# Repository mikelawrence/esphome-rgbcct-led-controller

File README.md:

# ESPHome RGBCCT LED Controller

<p align="center">
  
</p>

This project evolved from the need to support LED strips for growing African Violets. It is surprising how much light plants need and how little light LED strip actually put out. My original approach was three strips composed of Cool White (CW) and Warm White LEDs (WW). But it wasn't until I purchased a Photosynthetically Active Radiation (PAR) meter to measure the Photosynthetic Photon Flux Density (PPFD, units µmol/m²/s) just how un-bright my setup was. These units are interesting. The first part, µmol, is a number, specifically one-millionth of a mole, or 6.022 x 10²³ / 1,000,000 or 6.022 x 10¹⁷. The second part is an area, 1 meter squared. And finally time in seconds. When put together it is basically the number of photons striking a one meter squared area per second. Most measurements of light intensity, like lux, lumens, or luminance, are based on human perception are not really good for plants so PAR/PPFD was developed in the 1970s by Dr. Keith McCree. When I measured the light output of my setup with my shiny new PAR meter I got 20PPFD with my original setup of three strips of CW and WW LEDs between 60 and 200PPFD. There is different and sometimes conflicting information on the Internet but the range I found for African Violets is somewhere between 60 and 200PPFD. So my setup was three times less than minimum of 60PPFD.

Clearly I need more light. I started looking on Internet for "brighter" LED strips. I found [these](https://www.superlightingled.com/dc24v-112ledsm-highest-density-5in1-rgbww-led-strip-smd5050-164ft-p-5599.html) from SUPERLIGHTINGLED they have 5 different LEDS, Red, Green, Blue, Warm White and Cool Light. This is five PWM channels which reduces the available controllers to only a few but I did find a Zigbee 5-channel controller. But the control of the LEDs are difficult. What I really needed was to turn on all LEDS simultaneously and this controller could not so this with Home Assistant. It also adjust the light intensity with gamma which again is based on human perception. I found another controller from GLEDOPTO with WLED installed which gave me chance to control everything in the way I wanted and that is when I realized turning all the LEDS on at the same time caused them to warm up to more than 50°C. Not necessarily a problem but one that would probably shorten the life of the strips. I ended up with five of these LED strips per shelf running at a reduced intensity and still have 80PPFD.

Now that the light levels are in better range I decided to design my own LED controller because I wanted to add 4-Pin computer fan control and temperature measurement of both ambient and some of the LED strips to make sure I wasn't getting them too hot.

This LED controller supports the following:

* ESP32-S3
* ESPHome software development
* USB-C Interface for initial/ongoing programming, OTA will still be the primary mean of programming
* Power, Voltage and Current measurement with an INA232
* 5-Channel PWM LED control
* Supporting 5-24V Vin, this same voltage is applied to the LED and fan
* Two configurations: One supporting 5A and with the addition of two transistors 10A total current
* Each channel comfortably supports 2A simultaneous and up to 3-4A singly
* Vin is well protected
  * No damage input range is ±33V, TVS will adsorb higher transients
  * Over current shutdown
  * Over temperature shutdown
  * Short circuit shutdown
  * Reverse Polarity shutdown
  * Over Voltage Lockout
  * Under Voltage Lockout
* PCB temperature measurement near the Vin protection circuit. This is broken.
* Each channel is a protected MOSFET, if will shutdown when over temperature and will take a short to ground without damage
* With the addition of an expansion board
  * LED strip temperature measurement with 10K thermistors.
  * Ambient temperature measurement with a commonly available SHTXX I²C sensor

## Main PCB

<p align="center">
  
</p>

View the [README](pcb/README.md) for more information about this PCB.

## Temperature Expansion PCBs

<p align="center">

</p>

View the [Rev A README](pcb-expansion-rev-a/README.md) or [Rev B README](pcb-expansion-rev-b/README.md) for more information.

## Configuration

[RGBCCT LED Controller GH Pages](https://mikelawrence.github.io/esphome-rgbcct-led-controller/) provides installation and Home Assistant configuration support.

## Web Server

Th Web Server is enabled in the current configuration. The default username is `light` and password is `password`. Auth is enabled mainly because manual firmware updates are enabled in the Web Server.

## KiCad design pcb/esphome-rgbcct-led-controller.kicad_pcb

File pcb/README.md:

# ESPHome RGBCCT LED Controller PCB

The PCB is designed in [KiCad](https://www.kicad.org/). Fabrication and is tuned toward [JCLPCB](https://jlcpcb.com/). I using my [Whizoo Controleo3](https://whizoo.com/) oven to handle all but the Thru-Hole stuff which is hand soldered.

* **Rev A**: Has been fabricated, assembled, tested and is use in four places. There is one issue TMP1075 (U1) is connected to VINP and will burn when powered by 24V and must be left off the PCB.

## Testing Notes

Only the 5A configuration has been tested. Short circuit on LED outputs will not damage the board but the red LED will not light up. This type of short circuits will recover automatically recover when removed. Short circuits on the fan connector will shut off power to everything and cause the red LED to light up. Short circuits of this type are latching and require power-cycling to release. Over-voltage and Under-Voltage Lock Out work fine. The 4-Pin fan connector supports fans but the PWM signal is 1.5kHz well below the recommended 25kHz. There seems to be an issue with the ledc component the prevents different pwm frequencies when using 6 ledc channels. 1.5kHz work well with Noctua fans.

## Schematic

<p align="center">
     <br />
    Schematic
</p>

### Do Not Populate (DNP) Notes

TMP1075 (U1) cannot be populated due to a PCB error. It will burn with 24V Vin.

## Bill of Materials

<p align="center">
     <br />
    Interactive BOM
</p>

## PCB Info

* 6 layers with many vias to support high currents. Vias should be filled to improve thermals.
* Two configurations, 5A Continuous, 10A Short Circuit and 10A Continuous and 20A Short Circuit.
* Dimensions are 100mm X 45mm.
* Requires oven reflow or hot air to assemble most components.

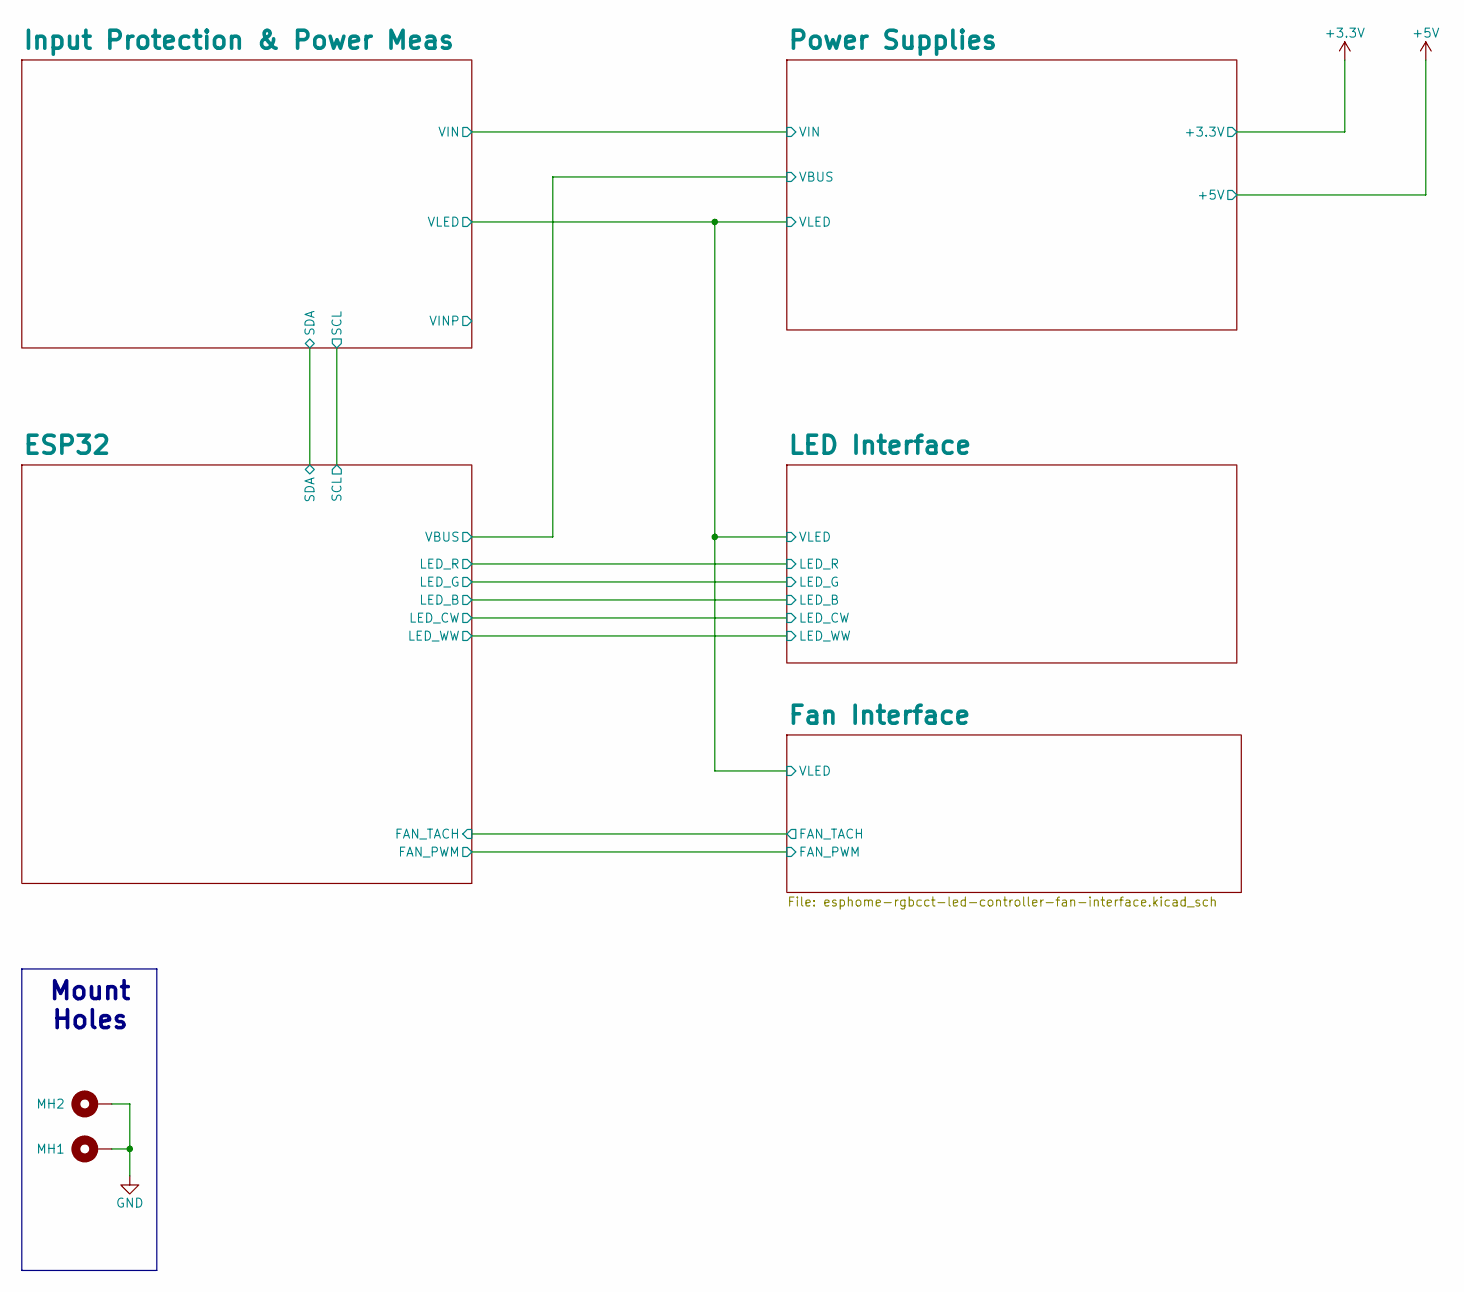
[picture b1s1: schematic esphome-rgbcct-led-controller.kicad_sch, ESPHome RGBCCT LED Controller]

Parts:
MH1, MH2: 97730606332R; Part Number 97730606332R

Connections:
GND: MH1.1 (1_1), MH2.1 (1_1); also elsewhere on the board

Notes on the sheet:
Mount Holes

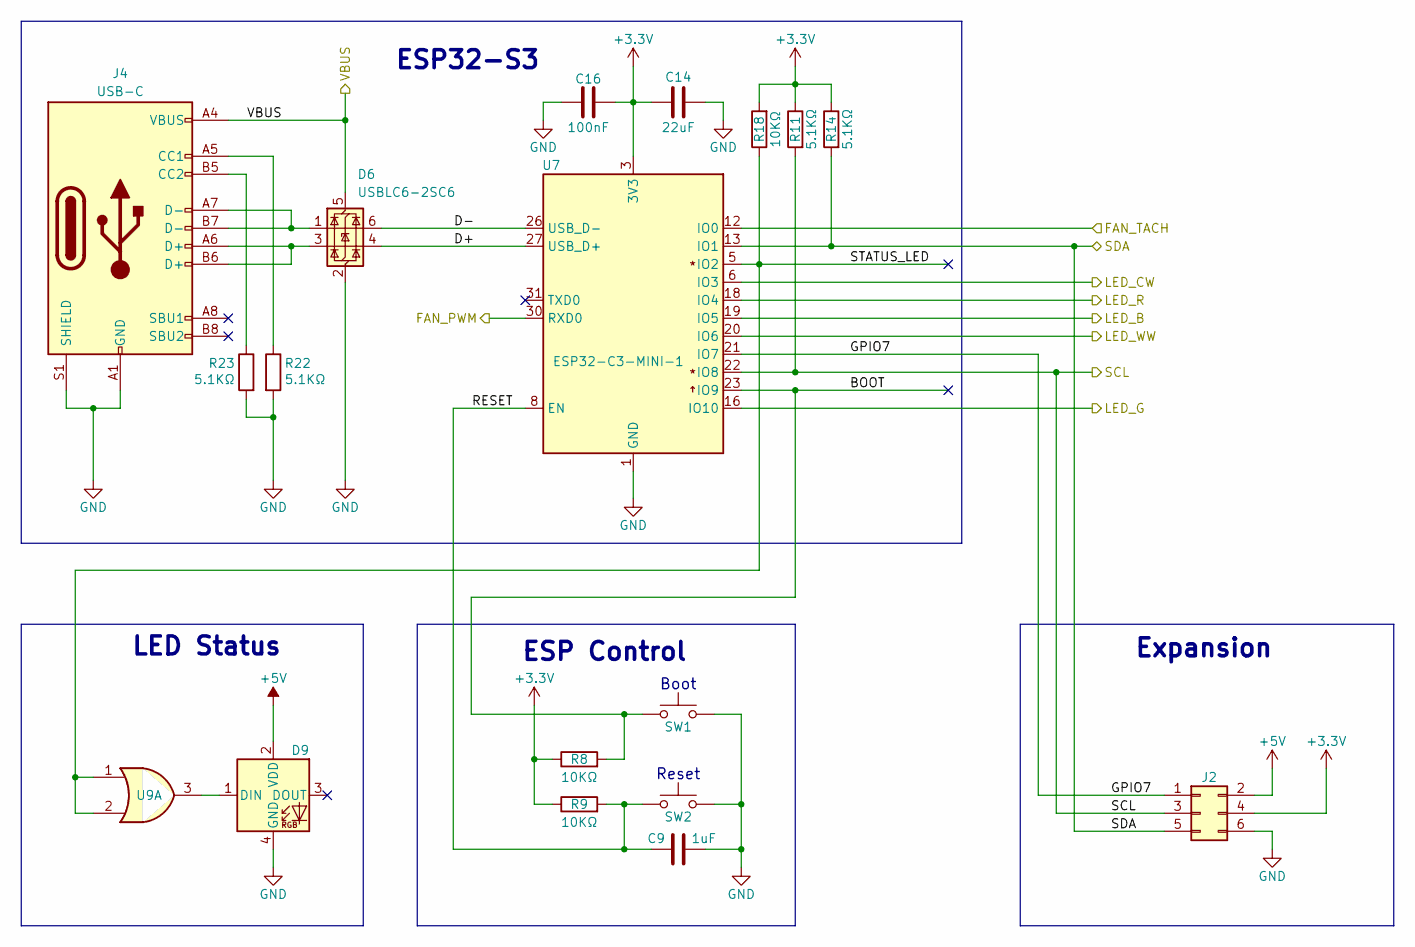
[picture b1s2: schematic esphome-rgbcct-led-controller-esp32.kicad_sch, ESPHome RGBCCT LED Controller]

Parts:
C9: 1uF; C_0402_1005Metric; Part Number GRM155R61H105KE05D
C14: 22uF; C_0603_1608Metric; Part Number GRM188R60J226MEA0D
C16: 100nF; C_0402_1005Metric; Part Number CL05B104KB54PNC
D6: USBLC6-2SC6; SOT-23-6; Part Number USBLC6-2SC6
D9: SK6812-4020; Part Number 4691
J2: SAMTEC_SFMC-103-01-L-D; Part Number SFMC-103-01-L-D
J4: USB-C; HRO_TYPE-C-31-M-12; Part Number 1332645
R8, R9, R18: 10KΩ; R_0402_1005Metric; Part Number CRCW040210K0FKED
R11, R14, R22, R23: 5.1KΩ; R_0402_1005Metric; Part Number CRCW04025K10FKED
SW1, SW2: SW_SPST_B3U-1000P-B; Part Number B3U-1000P
U7: ESP32-C3-MINI-1; ESP32-C3-MINI-1-N4X; Part Number ESP32-C3-MINI-1-N4X
U9: 74AHCT32; DHWQFN-14-1EP_2.5x3mm_P0.5mm_EP1x1.5mm; Part Number SN74AHCT32BQAR

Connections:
+3.3V: C14.1, C16.2, J2.4, R8.1, R9.1, R11.1, R14.1, R18.2, U7.3 (3V3); also elsewhere on the board
+5V: D9.2 (VDD), J2.2; also elsewhere on the board
/ESP32/BOOT: R8.2, SW1.2, U7.23 (IO9)
/ESP32/D+: D6.4 (I/O2), U7.27 (USB_D+)
/ESP32/D-: D6.6 (I/O1), U7.26 (USB_D-)
/ESP32/FAN_PWM: U7.30 (RXD0); also elsewhere on the board
/ESP32/FAN_TACH: U7.12 (IO0); also elsewhere on the board
/ESP32/GPIO7: J2.1, U7.21 (IO7)
/ESP32/LED_B: U7.19 (IO5); also elsewhere on the board
/ESP32/LED_CW: U7.6 (IO3); also elsewhere on the board
/ESP32/LED_G: U7.16 (IO10); also elsewhere on the board
/ESP32/LED_R: U7.18 (IO4); also elsewhere on the board
/ESP32/LED_WW: U7.20 (IO6); also elsewhere on the board
/ESP32/RESET: C9.1, R9.2, SW2.2, U7.8 (EN)
/ESP32/SCL: J2.3, R11.2, U7.22 (IO8); also elsewhere on the board
/ESP32/SDA: J2.5, R14.2, U7.13 (IO1); also elsewhere on the board
/ESP32/STATUS_LED: R18.1, U7.5 (IO2), U9.1, U9.2
/ESP32/VBUS: D6.5 (VBUS), J4.A4 (VBUS), J4.B4 (VBUS); also elsewhere on the board
GND: C9.2, C14.2, C16.1, D6.2 (GND), D9.4 (GND), J2.6, J4.A1 (GND), J4.B1 (GND), J4.S1 (SHIELD), R22.2, R23.2, SW1.1, SW2.1, U7.1 (GND), U7.2 (GND), U7.11 (GND), U7.14 (GND), U7.36 (GND), U7.37 (GND), U7.38 (GND), U7.39 (GND), U7.40 (GND), U7.41 (GND), U7.42 (GND), U7.43 (GND), U7.44 (GND), U7.45 (GND), U7.46 (GND), U7.47 (GND), U7.48 (GND), U7.49 (GND), U7.50 (GND), U7.51 (GND), U7.52 (GND), U7.53 (GND); also elsewhere on the board
unnamed: D6.1 (I/O1), J4.A7 (D-), J4.B7 (D-)
unnamed: D6.3 (I/O2), J4.A6 (D+), J4.B6 (D+)
unnamed: D9.1 (DIN), U9.3
unnamed: J4.A5 (CC1), R22.1
unnamed: J4.B5 (CC2), R23.1

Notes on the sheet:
ESP32-S3
Expansion
Reset
ESP Control
Boot
LED Status

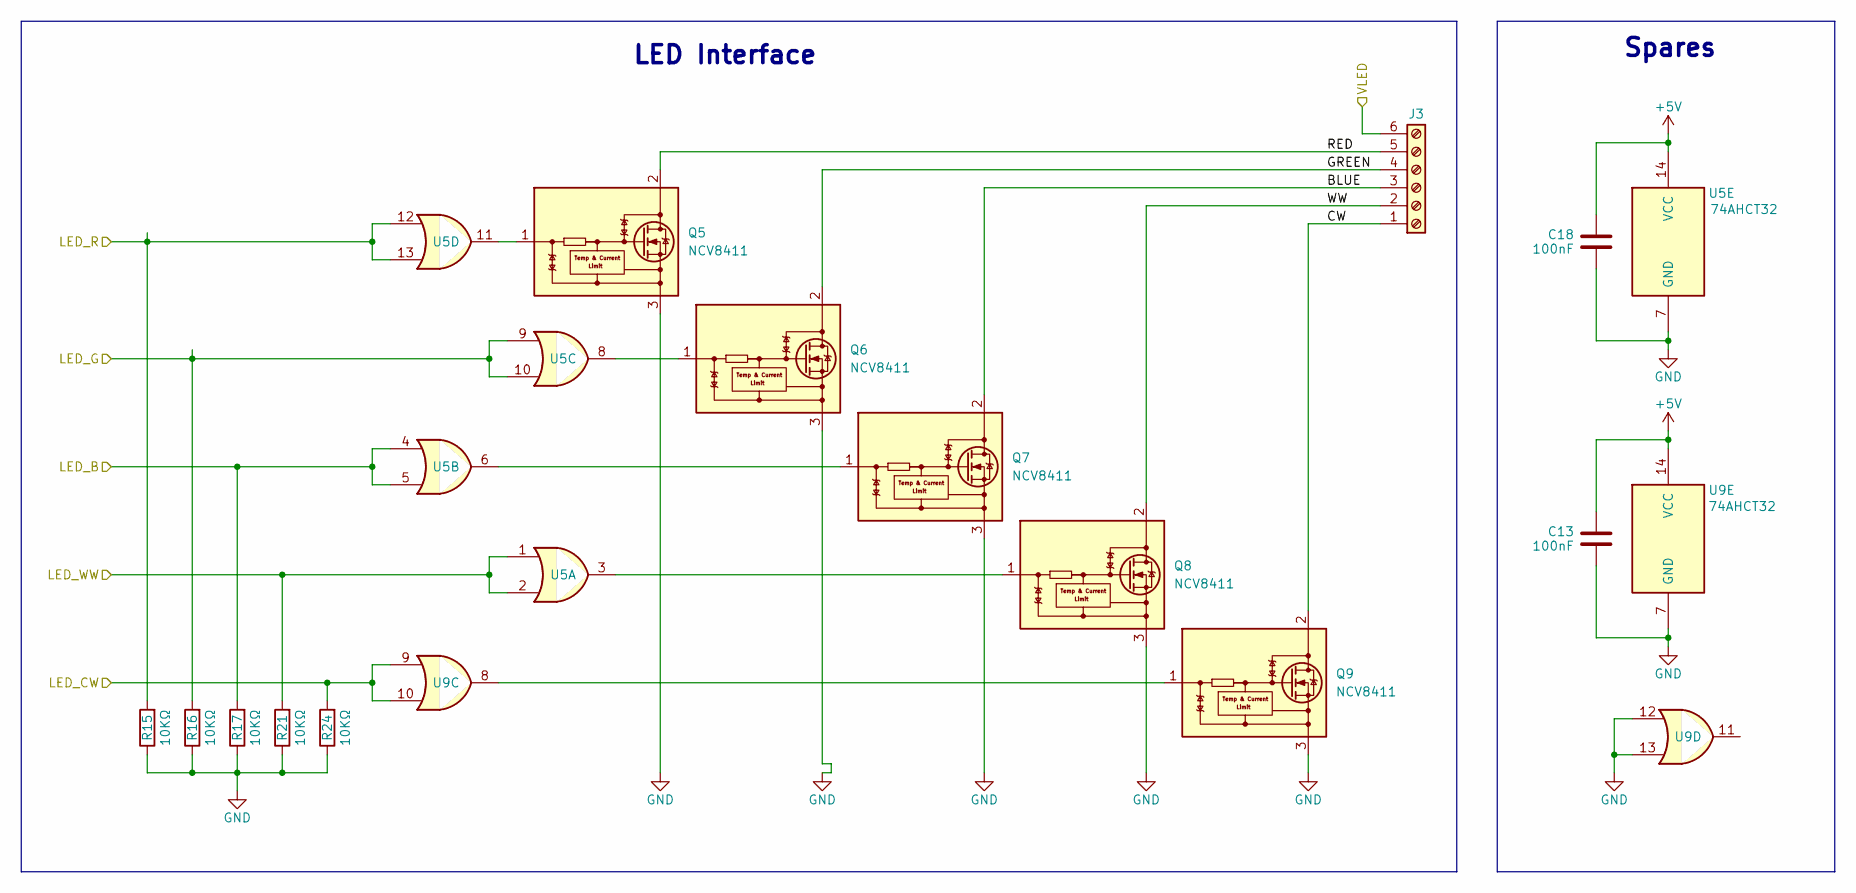
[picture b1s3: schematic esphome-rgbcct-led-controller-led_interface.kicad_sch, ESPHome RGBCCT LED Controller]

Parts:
C13, C18: 100nF; C_0402_1005Metric; Part Number CL05B104KB54PNC
J3: 1017507; Part Number 1017507
Q5, Q6, Q7, Q8, Q9: NCV8411; TO-252-2; Part Number NCV8411DTRKG
R15, R16, R17, R21, R24: 10KΩ; R_0402_1005Metric; Part Number CRCW040210K0FKED
U5, U9: 74AHCT32; DHWQFN-14-1EP_2.5x3mm_P0.5mm_EP1x1.5mm; Part Number SN74AHCT32BQAR

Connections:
+5V: C13.1, C18.1, U5.14 (VCC), U9.14 (VCC); also elsewhere on the board
/ESP32/LED_B: R17.2, U5.4, U5.5; also elsewhere on the board
/ESP32/LED_CW: R24.2, U9.9, U9.10; also elsewhere on the board
/ESP32/LED_G: R16.2, U5.9, U5.10; also elsewhere on the board
/ESP32/LED_R: R15.2, U5.12, U5.13; also elsewhere on the board
/ESP32/LED_WW: R21.2, U5.1, U5.2; also elsewhere on the board
/Fan Interface/VLED: J3.6; also elsewhere on the board
/LED Interface/BLUE: J3.3, Q7.2 (D)
/LED Interface/CW: J3.1, Q9.2 (D)
/LED Interface/GREEN: J3.4, Q6.2 (D)
/LED Interface/RED: J3.5, Q5.2 (D)
/LED Interface/WW: J3.2, Q8.2 (D)
GND: C13.2, C18.2, Q5.3 (S), Q6.3 (S), Q7.3 (S), Q8.3 (S), Q9.3 (S), R15.1, R16.1, R17.1, R21.1, R24.1, U5.7 (GND), U9.7 (GND), U9.12, U9.13; also elsewhere on the board
unnamed: Q5.1 (G), U5.11
unnamed: Q6.1 (G), U5.8
unnamed: Q7.1 (G), U5.6
unnamed: Q8.1 (G), U5.3
unnamed: Q9.1 (G), U9.8

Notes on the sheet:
Spares
LED Interface

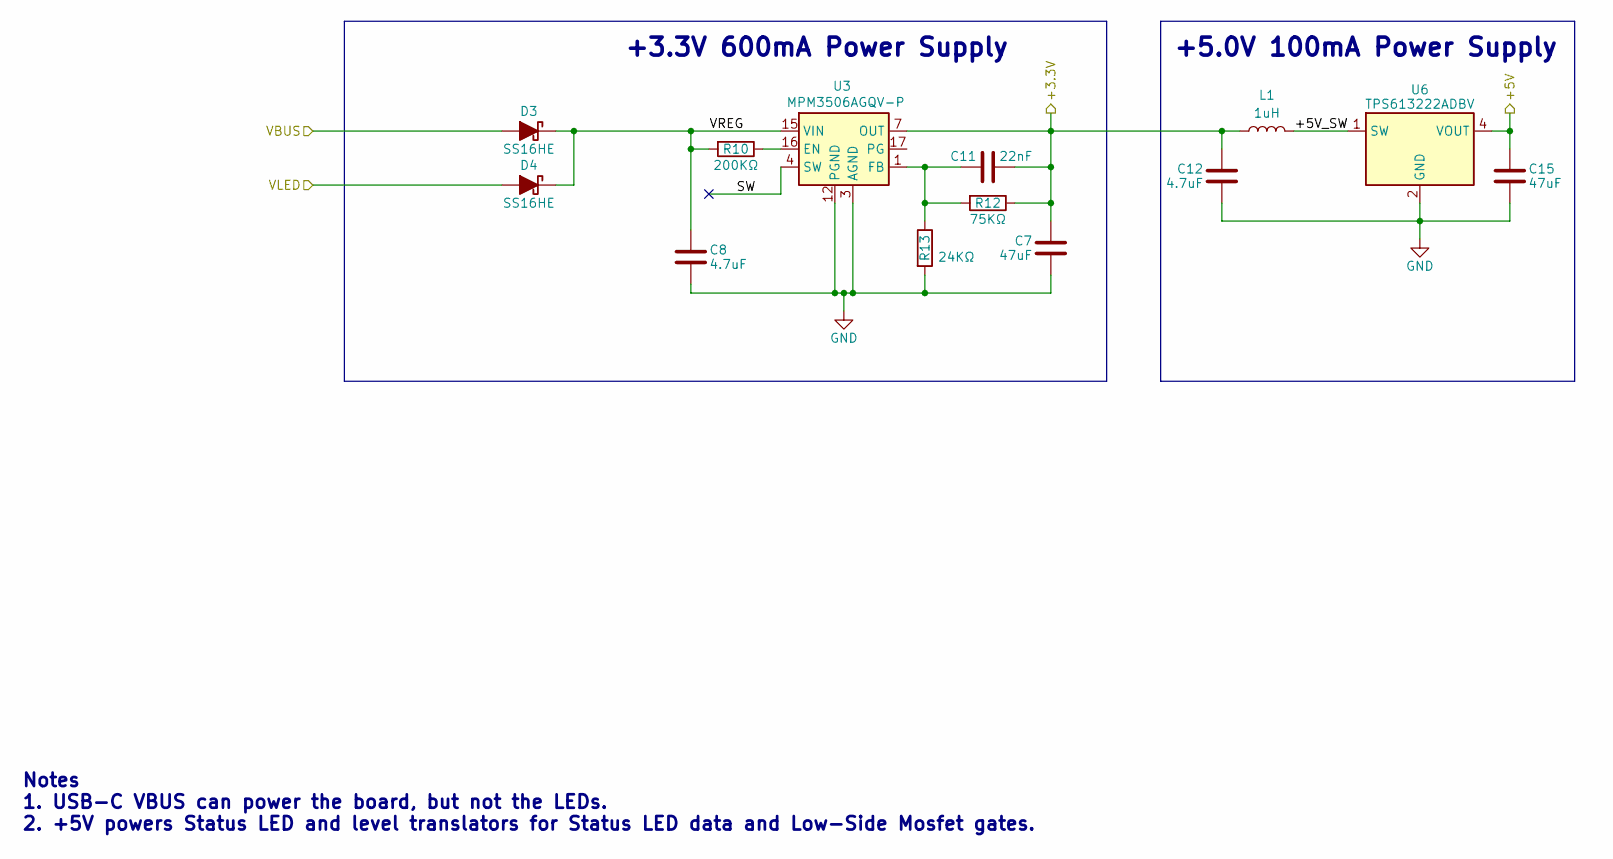
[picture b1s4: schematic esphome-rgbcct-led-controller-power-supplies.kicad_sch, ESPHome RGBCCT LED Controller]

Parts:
C7, C15: 47uF; C_0805_2012Metric; Part Number MSASL21GBB5476MTNA01
C8, C12: 4.7uF; C_0805_2012Metric; Part Number MSASU21GBB5475KTNA01
C11: 22nF; C_0402_1005Metric; Part Number GRM155R71H223KA12J
D3, D4: SS16HE; Part Number SS16HE
L1: 1uH; L_0805_2012Metric; Part Number MLP2012S1R0MT0S1
R10: 200KΩ; R_0402_1005Metric; Part Number CRCW0402200KFKED
R12: 75KΩ; R_0402_1005Metric; Part Number RT0402BRD0775KL
R13: 24KΩ; R_0402_1005Metric; Part Number RT0402BRD0724KL
U3: MPM3506AGQV-P; QFN-19; Part Number MPM3506AGQV-P; Mouser Part Number 946-MPM3506AGQV-P
U6: TPS613222ADBV; SOT-23-5; Part Number TPS613222ADBVR

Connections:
+3.3V: C7.1, C11.2, C12.1, L1.1, R12.1, U3.7 (OUT), U3.8 (OUT_2), U3.9 (OUT_3), U3.19 (OUT_4); also elsewhere on the board
+5V: C15.1, U6.4 (VOUT); also elsewhere on the board
/ESP32/VBUS: D3.2 (A); also elsewhere on the board
/Fan Interface/VLED: D4.2 (A); also elsewhere on the board
/Power Supplies/+5V_SW: L1.2, U6.1 (SW)
/Power Supplies/SW: U3.4 (SW), U3.5 (SW_2), U3.6 (SW_3), U3.18 (SW_4)
/Power Supplies/VREG: C8.1, D3.1 (K), D4.1 (K), R10.2, U3.15 (VIN)
GND: C7.2, C8.2, C12.2, C15.2, R13.2, U3.3 (AGND), U3.12 (PGND), U3.13 (PGND_2), U6.2 (GND); also elsewhere on the board
unnamed: R10.1, U3.16 (EN)
unnamed: C11.1, R12.2, R13.1, U3.1 (FB)

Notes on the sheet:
+5.0V 100mA Power Supply
+3.3V 600mA Power Supply
Notes 1. USB-C VBUS can power the board, but not the LEDs. 2. +5V powers Status LED and level translators for Status LED data and Low-Side Mosfet gates.

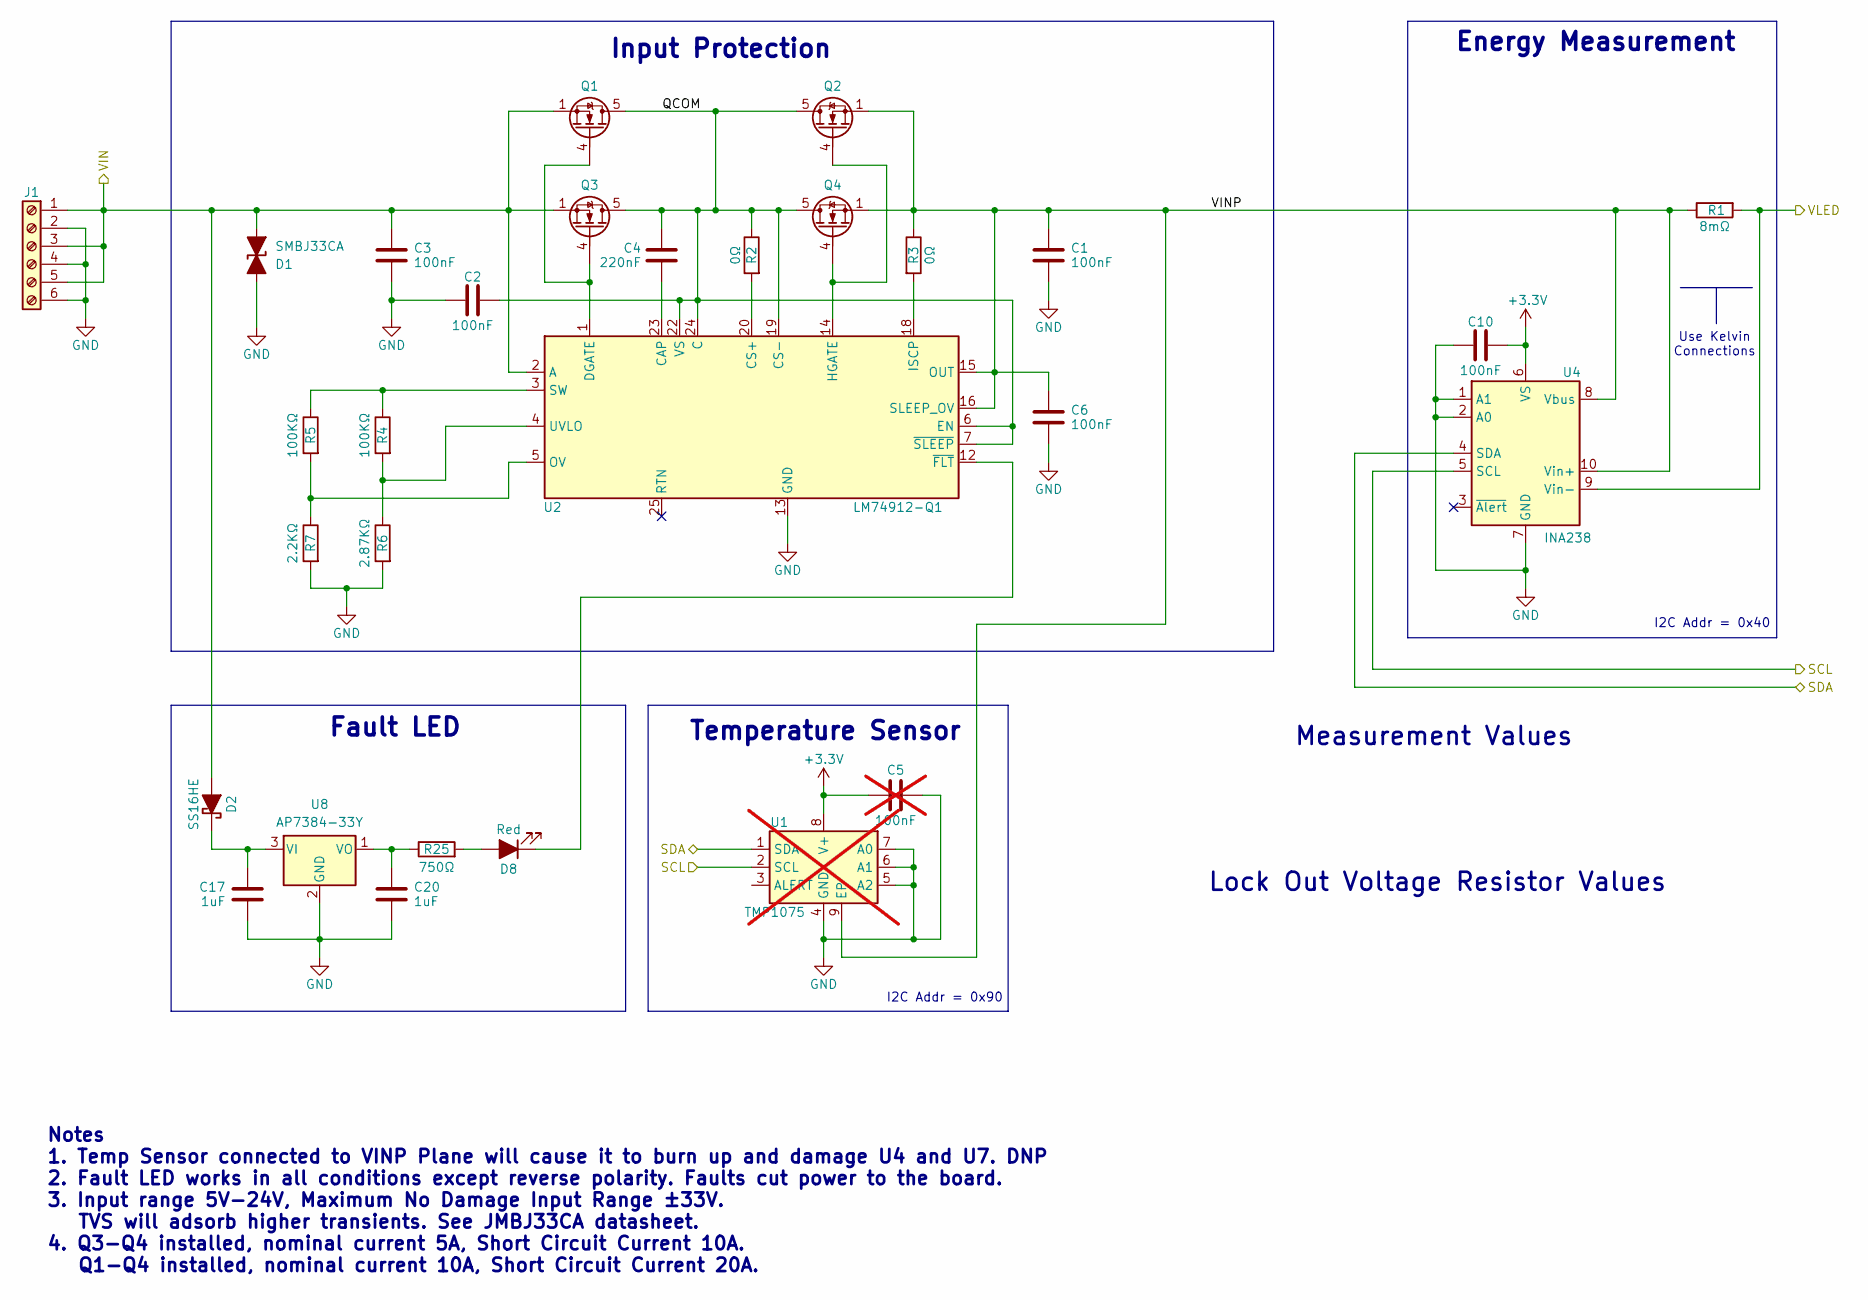
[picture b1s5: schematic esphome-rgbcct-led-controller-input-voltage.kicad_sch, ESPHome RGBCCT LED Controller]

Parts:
C1, C2, C3, C6, C10: 100nF; C_0402_1005Metric; Part Number CL05B104KB54PNC
C4: 220nF; C_0402_1005Metric; Part Number GRM155R61H224ME01W
C5: 100nF; C_0402_1005Metric; Part Number CL05B104KB54PNC; not fitted
C17, C20: 1uF; C_0402_1005Metric; Part Number GRM155R61H105KE05D
D1: SMBJ33CA; D_SMB; Part Number SMBJ33CA
D2: SS16HE; Part Number SS16HE
D8: Red; APDA3020LSECKJ3PF; Part Number APDA3020LSECK/J3-PF
J1: 1017505; 1017507; Part Number 1017505
Q1, Q2, Q3, Q4: TQM050NB06CR; TRANS_TQM050NB06CR_RLG; Part Number TQM050NB06CR RLG
R1: 8mΩ; R_2512_6332Metric; Part Number MSMA2512R0080FGM
R2, R3: 0Ω; R_0402_1005Metric; Part Number RC0402FR-070RL
R4, R5: 100KΩ; R_0402_1005Metric; Part Number RT0402BRD07100KL
R6: 2.87KΩ; R_0402_1005Metric; Part Number RT0402BRD072K87L
R7: 2.2KΩ; R_0402_1005Metric; Part Number RT0402BRD072K2L
R25: 750Ω; R_0402_1005Metric; Part Number CRCW0402750RFKED
U1: TMP1075; WSON-8-1EP_2x2mm_P0.5mm_EP0.9x1.6mm_ThermalVias; Part Number TMP1075DSGR; not fitted
U2: LM74912-Q1; Texas_RGE0024C_VQFN-24-1EP_4x4mm_P0.5mm_EP2.1x2.1mm; Part Number LM74912QRGERQ1
U4: INA238; VSSOP-10_3x3mm_P0.5mm; Part Number INA238AIDGSR
U8: AP7384-33Y; SOT-89-3; Part Number AP7384-33Y-13

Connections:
+3.3V: C5.2, C10.2, U1.8 (V+), U4.6 (VS); also elsewhere on the board
/ESP32/SCL: U1.2 (SCL), U4.5 (SCL); also elsewhere on the board
/ESP32/SDA: U1.1 (SDA), U4.4 (SDA); also elsewhere on the board
/Fan Interface/VLED: R1.2, U4.9 (Vin-); also elsewhere on the board
/Input Protection & Power Meas/QCOM: C2.2, C4.2, Q1.5 (D), Q2.5 (D), Q3.5 (D), Q4.5 (D), R2.1, U2.6 (EN), U2.7 (~SLEEP), U2.19 (CS-), U2.22 (VS), U2.24 (C)
/Input Protection & Power Meas/VIN: C3.1, D1.1 (A1), D2.2 (A), J1.1, J1.3, J1.5, Q1.1 (S), Q1.2 (S), Q1.3 (S), Q3.1 (S), Q3.2 (S), Q3.3 (S), U2.2 (A)
/Input Protection & Power Meas/VINP: C1.1, C6.1, Q2.1 (S), Q2.2 (S), Q2.3 (S), Q4.1 (S), Q4.2 (S), Q4.3 (S), R1.1, R3.1, U1.9 (EP), U2.15 (OUT), U2.16 (SLEEP_OV), U4.8 (Vbus), U4.10 (Vin+)
GND: C1.2, C2.1, C3.2, C5.1, C6.2, C10.1, C17.2, C20.2, D1.2 (A2), J1.2, J1.4, J1.6, R6.2, R7.2, U1.4 (GND), U1.5 (A2), U1.6 (A1), U1.7 (A0), U2.13 (GND), U4.1 (A1), U4.2 (A0), U4.7 (GND), U8.2 (GND); also elsewhere on the board
unnamed: C17.1, D2.1 (K), U8.3 (VI)
unnamed: D8.2 (A), R25.2
unnamed: D8.1 (K), U2.12 (~FLT)
unnamed: Q1.4 (G), Q3.4 (G), U2.1 (DGATE)
unnamed: Q2.4 (G), Q4.4 (G), U2.14 (HGATE)
unnamed: C4.1, U2.23 (CAP)
unnamed: R2.2, U2.20 (CS+)
unnamed: R3.2, U2.18 (ISCP)
unnamed: R5.2, R7.1, U2.5 (OV)
unnamed: R4.1, R5.1, U2.3 (SW)
unnamed: R4.2, R6.1, U2.4 (UVLO)
unnamed: C20.1, R25.1, U8.1 (VO)

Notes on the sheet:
I2C Addr = 0x40
Energy Measurement
Notes 1. Temp Sensor connected to VINP Plane will cause it to burn up and damage U4 and U7. DNP 2. Fault LED works in all conditions except reverse polarity. Faults cut power to the board. 3. Input range 5V-24V, Maximum No Damage Input Range ±33V. TVS will adsorb higher transients. See JMBJ33CA dat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
I2C Addr = 0x90
Fault LED
Temperature Sensor
Input Protection
Measurement Values
Use Kelvin Connections
Lock Out Voltage Resistor Values

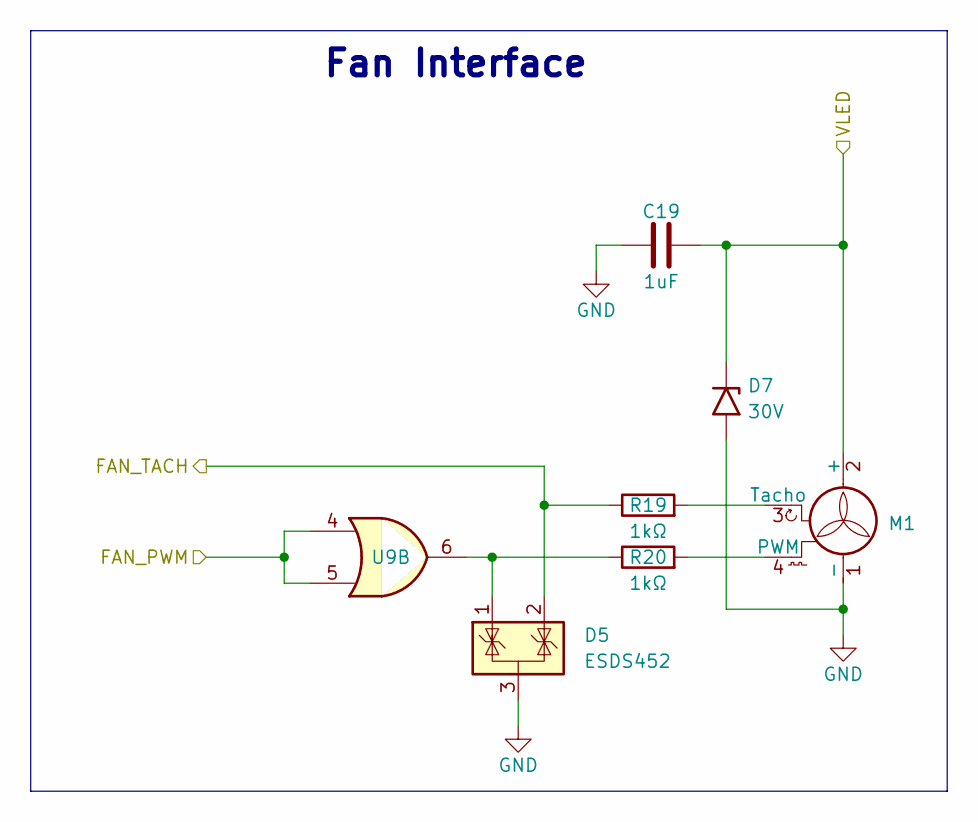
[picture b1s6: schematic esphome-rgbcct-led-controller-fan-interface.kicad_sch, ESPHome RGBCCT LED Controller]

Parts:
C19: 1uF; C_0402_1005Metric; Part Number GRM155R61H105KE05D
D5: ESDS452; SOT-23; Part Number ESDS452DBZR
D7: 30V; D_SMA; Part Number SMAJ30CA-13-F
M1: Fan_CPU_4pin; FanPinHeader_1x04_P2.54mm_Vertical; Part Number 47053-1000
R19, R20: 1kΩ; R_0402_1005Metric; Part Number CRCW04021K00FKED
U9: 74AHCT32; DHWQFN-14-1EP_2.5x3mm_P0.5mm_EP1x1.5mm; Part Number SN74AHCT32BQAR

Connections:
/ESP32/FAN_PWM: U9.4, U9.5; also elsewhere on the board
/ESP32/FAN_TACH: D5.2 (K), R19.1; also elsewhere on the board
/Fan Interface/VLED: C19.2, D7.1 (A1), M1.2 (+); also elsewhere on the board
GND: C19.1, D5.3 (A), D7.2 (A2), M1.1 (-); also elsewhere on the board
unnamed: D5.1 (K), R20.1, U9.6
unnamed: M1.4 (PWM), R20.2
unnamed: M1.3 (Tacho), R19.2

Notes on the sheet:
Fan Interface

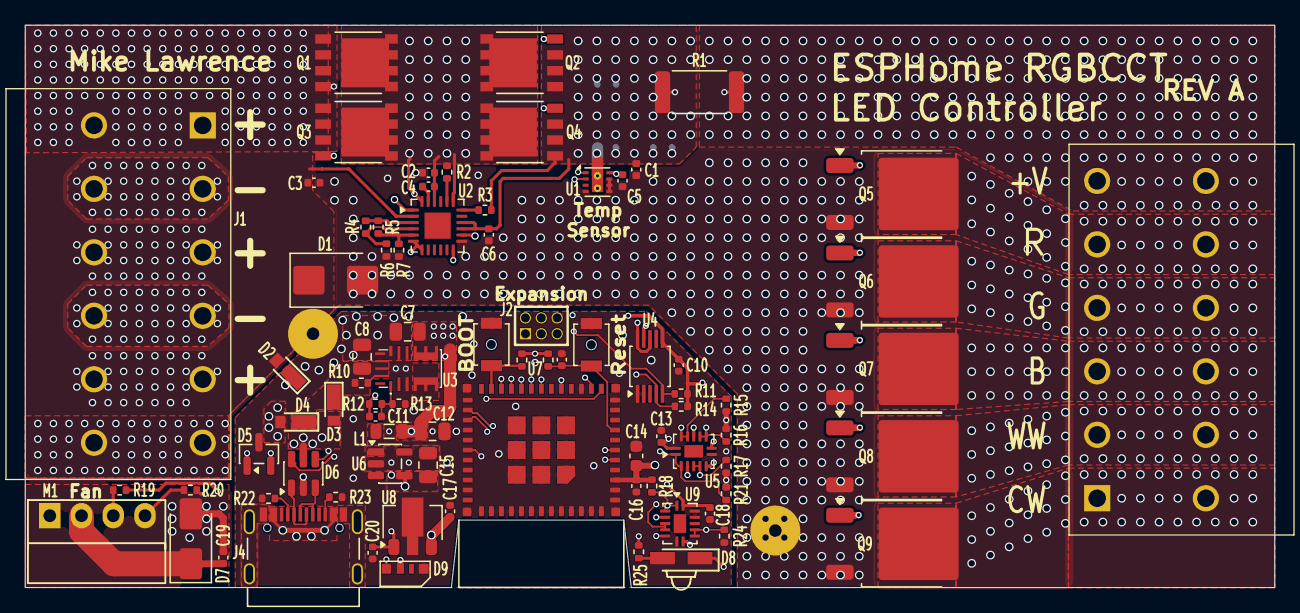
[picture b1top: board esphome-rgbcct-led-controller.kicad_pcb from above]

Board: 6 copper layers, 100.0 x 45.0 mm, 83 parts (1 on the bottom side), 58 nets.

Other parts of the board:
TEXT1: OSHW-Logo_5.7x6mm_SilkScreen

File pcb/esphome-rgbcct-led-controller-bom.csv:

"Qty","Reference","Value","Description","Datasheet","Footprint","DNP","Manufacturer","Part Number"
"9","C1,C2,C3,C5,C6,C10,C13,C16,C18","100nF","Capacitor, 100nF, MLCC, 50V, X7R, 10%, 0402","","Capacitor_SMD:C_0402_1005Metric","DNP","Samsung","CL05B104KB54PNC"
"1","C4","220nF","Capacitor, 220nF, MLCC, 50V, X5R, 20%, 0402","","Capacitor_SMD:C_0402_1005Metric","","Murata","GRM155R61H224ME01W"
"2","C7,C15","47uF","Capacitor, 47uF, MLCC, 10V, X5R, 20%, 0805","","Capacitor_SMD:C_0805_2012Metric","","TAIYO YUDEN","MSASL21GBB5476MTNA01"
"2","C8,C12","4.7uF","Capacitor, 4.7uF, MLCC, 50V, X5R, 20%, 0805","","Capacitor_SMD:C_0805_2012Metric","","TAIYO YUDEN","MSASU21GBB5475KTNA01"
"4","C9,C17,C19,C20","1uF","Capacitor, 1uF, MLCC, 50V, X5R, 10%, 0402","","Capacitor_SMD:C_0402_1005Metric","","Murata","GRM155R61H105KE05D"
"1","C11","22nF","Capacitor, 22nF, MLCC, 50V, X7R, 10%, 0402","","Capacitor_SMD:C_0402_1005Metric","","Murata","GRM155R71H223KA12J"
"1","C14","22uF","Capacitor, 22uF, MLCC, 6.3V, X5R, 20%, 0603","","Capacitor_SMD:C_0603_1608Metric","","Murata","GRM188R60J226MEA0D"
"1","D1","SMBJ33CA","Bidirectional transient-voltage-suppression diode, filled shape","","Diode_SMD:D_SMB","","Bourns","SMBJ33CA"
"3","D2,D3,D4","SS16HE","Schottky Diode, 60V, 1A, SOD-323EP","https://www.onsemi.com/pdf/datasheet/ss13he-d.pdf","SS16HE:SS16HE","","OnSemi","SS16HE"
"1","D5","ESDS452","5.5-V Bi-Directional TVS Diode","https://www.ti.com/lit/ds/symlink/esds452.pdf","Package_TO_SOT_SMD:SOT-23","","Texas Instruments","ESDS452DBZR"
"1","D6","USBLC6-2SC6","Very low capacitance ESD protection diode, 2 data-line, SOT-23-6","https://www.st.com/resource/en/datasheet/usblc6-2.pdf","Package_TO_SOT_SMD:SOT-23-6","","STMicroelectronics","USBLC6-2SC6"
"1","D7","30V","400W unidirectional Transient Voltage Suppressor, 30.0Vr, SMA(DO-214AC)","https://www.littelfuse.com/media?resourcetype=datasheets&ite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","Diode_SMD:D_SMA","","Diodes Incorporated","SMAJ30CA-13-F "
"1","D8","Red","Light emitting diode, filled shape","https://www.kingbrightusa.com/images/catalog/SPEC/APDA3020LS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","APDA3020LSECK_J3-PF:APDA3020LSECKJ3PF","","Kingbright","APDA3020LSECK/J3-PF"
"1","D9","SK6812-4020","RGB LED with integrated controller, 4mm x 2mm Side LED package","https://cdn-shop.adafruit.com/product-files/4691/4691_SK68XX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","SK6812-4020:SK6812-4020","","Adafruit","4691"
"1","J1","1017505","Terminal Block, 12-24 AWG, push-in connection, 4-position, 32A","https://www.mouser.com/datasheet/3/507/10/phoenix_contact_10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","1017507:1017507","","Phoenix Contact","1017505"
"1","J2","","Generic connector, double row, 02x03, odd/even pin numbering scheme (row 1 odd numbers, row 2 even numbers), script generated (kicad-library-utils/schlib/autogen/connector/)","","SAMTEC_SFMC10301LD:SAMTEC_SFMC-103-01-L-D","","Samtec","SFMC-103-01-L-D"
"1","J3","1017507","Terminal Block, 12-24 AWG, push-in connection, 6-position, 32A","https://www.mouser.com/datasheet/3/507/10/phoenix_contact_10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","1017507:1017507","","Phoenix Contact","1017507"
"1","J4","USB-C","Connector, USB 2.0, 16P, Type-C, Receptacle","https://www.usb.org/sites/default/files/documents/usb_type-c.zip","TYPE-C-31-M-12:HRO_TYPE-C-31-M-12","","Phoenix Contact","1332645"
"1","L1","1uH","Inductor, 1uH, 3.3A, 20%, 1008","","Inductor_SMD:L_0805_2012Metric","","TDK","MLP2012S1R0MT0S1"
"1","M1","Fan_CPU_4pin","CPU Fan, tacho output, PWM input, 4-pin connector","http://www.formfactors.org/developer%5Cspecs%5Crev1_2_public.pdf","Connector:FanPinHeader_1x04_P2.54mm_Vertical","","Molex","47053-1000"
"2","MH1,MH2","","Mounting Hole with connection","https://www.we-online.com/components/products/datasheet/9773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","97730606332R:97730606332R","","Wurth","97730606332R"
"4","Q1,Q2,Q3,Q4","TQM050NB06CR","N-MOSFET transistor, 60V, 104A, 5mΩ, 3.8V Vgs, PDFN56U","https://services.taiwansemi.com/storage/resources/datasheet/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","TQM050NB06CR_RLG:TRANS_TQM050NB06CR_RLG","","Taiwan Semiconductor","TQM050NB06CR RLG"
"5","Q5,Q6,Q7,Q8,Q9","NCV8411","Self-Protected Low Side Driver with Temperature and Current Limit, TO-252-2","https://www.onsemi.com/pdf/datasheet/ncv8411-d.pdf","Package_TO_SOT_SMD:TO-252-2","","OnSemi","NCV8411DTRKG"
"1","R1","8mΩ","Current Sense Resistor, 8mΩ, 3W, 1%, 50ppm, 2512","","Resistor_SMD:R_2512_6332Metric","","Eaton Electronics","MSMA2512R0080FGM"
"2","R2,R3","0Ω","Resistor, 0Ω, 0402","","Resistor_SMD:R_0402_1005Metric","","YAGEO","RC0402FR-070RL"
"2","R4,R5","100KΩ","Resistor, 100KΩ, 62.5mW, 25PPM, 0.1%, 0402","","Resistor_SMD:R_0402_1005Metric","","YAGEO","RT0402BRD07100KL"
"1","R6","2.87KΩ","Resistor, 2.87KΩ, 62.5mW, 25PPM, 0.1%, 0402","","Resistor_SMD:R_0402_1005Metric","","YAGEO","RT0402BRD072K87L"
"1","R7","2.2KΩ","Resistor, 2.2KΩ, 62.5mW, 25PPM, 0.1%, 0402","","Resistor_SMD:R_0402_1005Metric","","YAGEO","RT0402BRD072K2L"
"8","R8,R9,R15,R16,R17,R18,R21,R24","10KΩ","Resistor, 10KΩ, 62.5mW,100PPM, 1%, 0402","","Resistor_SMD:R_0402_1005Metric","","Vishay / Dale","CRCW040210K0FKED"
"1","R10","200KΩ","Resistor, 200KΩ, 62.5mW,100PPM, 1%, 0402","","Resistor_SMD:R_0402_1005Metric","","Vishay / Dale","CRCW0402200KFKED"
"4","R11,R14,R22,R23","5.1KΩ","Resistor, 5.1KΩ, 62.5mW, 100ppm, 1%, 0402","","Resistor_SMD:R_0402_1005Metric","","Vishay / Dale","CRCW04025K10FKED"
"1","R12","75KΩ","Resistor, 75KΩ, 62.5mW, 25PPM, 0.1%, 0402","","Resistor_SMD:R_0402_1005Metric","","YAGEO","RT0402BRD0775KL"
"1","R13","24KΩ","Resistor, 24KΩ, 62.5mW, 25PPM, 0.1%, 0402","","Resistor_SMD:R_0402_1005Metric","","YAGEO","RT0402BRD0724KL"
"2","R19,R20","1kΩ","Resistor, 1KΩ, 62.5mW,100PPM, 1%, 0402","","Resistor_SMD:R_0402_1005Metric","","Vishay / Dale","CRCW04021K00FKED"
"1","R25","750Ω","Resistor, 750Ω, 62.5mW,100PPM, 1%, 0402","","Resistor_SMD:R_0402_1005Metric","","Vishay / Dale","CRCW0402750RFKED"
"2","SW1,SW2","","Switch, SMD","https://omronfs.omron.com/en_US/ecb/products/pdf/en-b3u.pdf","Button_Switch_SMD:SW_SPST_B3U-1000P-B","","Omron","B3U-1000P"
"1","U1","TMP1075","I2C-bus digital temperature sensor and thermal watchdog, WSON-8","https://www.ti.com/lit/gpn/tmp1075","Package_SON:WSON-8-1EP_2x2mm_P0.5mm_EP0.9x1.6mm_ThermalVias","DNP","Texas Instruments","TMP1075DSGR"
"1","U2","LM74912-Q1","Automotive Ideal Diode Controller With Fault Output and Overvoltage, Undervoltage, and Short Circuit Protection, VQFN-24","https://www.ti.com/lit/ds/symlink/lm74912-q1.pdf","Package_DFN_QFN:Texas_RGE0024C_VQFN-24-1EP_4x4mm_P0.5mm_EP2.1x2.1mm","","Texas Instruments","LM74912QRGERQ1"
"1","U3","MPM3506AGQV-P","Switching Voltage Regulators 36V/0.6A Module Sync Step-Down Converter","https://www.monolithicpower.com/pub/media/document/MPM3506A_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","MPM3506A:QFN-19","","Monolithic Power Systems","MPM3506AGQV-P"
"1","U4","INA238","IC, 85-V, 16-Bit, High-Precision Power Monitor With I2C Interface, VSSOP-10","https://www.ti.com/lit/ds/symlink/ina238.pdf","Package_SO:VSSOP-10_3x3mm_P0.5mm","","Texas Instruments","INA238AIDGSR"
"2","U5,U9","74AHCT32","Quad 2-input OR","https://www.ti.com/lit/ds/symlink/sn74ahct32.pdf","Package_DFN_QFN:DHWQFN-14-1EP_2.5x3mm_P0.5mm_EP1x1.5mm","","Texas Instruments","SN74AHCT32BQAR"
"1","U6","TPS613222ADBV","1.8A Step-Up Converter, 5V Output Voltage, 0.9-5.5V Input Voltage, SOT-23-5","http://www.ti.com/lit/ds/symlink/tps61322.pdf","Package_TO_SOT_SMD:SOT-23-5","","Texas Instruments","TPS613222ADBVR"
"1","U7","ESP32-C3-MINI-1","RF Module, ESP32-C3 SoC, Wi-Fi 802.11b/g/n, Bluetooth 5, BLE, 32-bit, 3.3V, onboard antenna, SMD","https://documentation.espressif.com/esp32-c3-mini-1_datashee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","ESP32-C3-MINI:ESP32-C3-MINI-1-N4X","","Espressif Systems","ESP32-C3-MINI-1-N4X"
"1","U8","AP7384-33Y","50mA Low Dropout Voltage Regulator, Fixed Output 3.3V, Wide Input Voltage Range 40V, SOT-89-3","https://www.diodes.com/assets/Datasheets/AP7384.pdf","Package_TO_SOT_SMD:SOT-89-3","","Diodes Inc","AP7384-33Y-13"
